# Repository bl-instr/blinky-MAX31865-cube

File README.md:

#    Blinky-MAX31864 Cube # 
The Blinky-MAX31865 cube is a precision 4 terminal resistance measurement device that integrates into a Blinky-Lite control platform. The cubes incorporates two [Adafruit MAX31865 breakout boards](https://www.adafruit.com/product/3648) providing two independent measurment channels with 15 bits of resolution

## Features: ##
- Seamless integration into the open source [Blinky-Lite control platform](https://www.blinky-lite.se/) 
- Wireless connection for data acquistion and control
- Web interface for wireless connection configuration
- Two independent channels
- Eighth order Chebyschev or power series temperature fit via web interface
- 100 mS pulsed measurements for low self heating
- User defined IIR filtering
- User defined measurement rate
- 15 bits of resolution

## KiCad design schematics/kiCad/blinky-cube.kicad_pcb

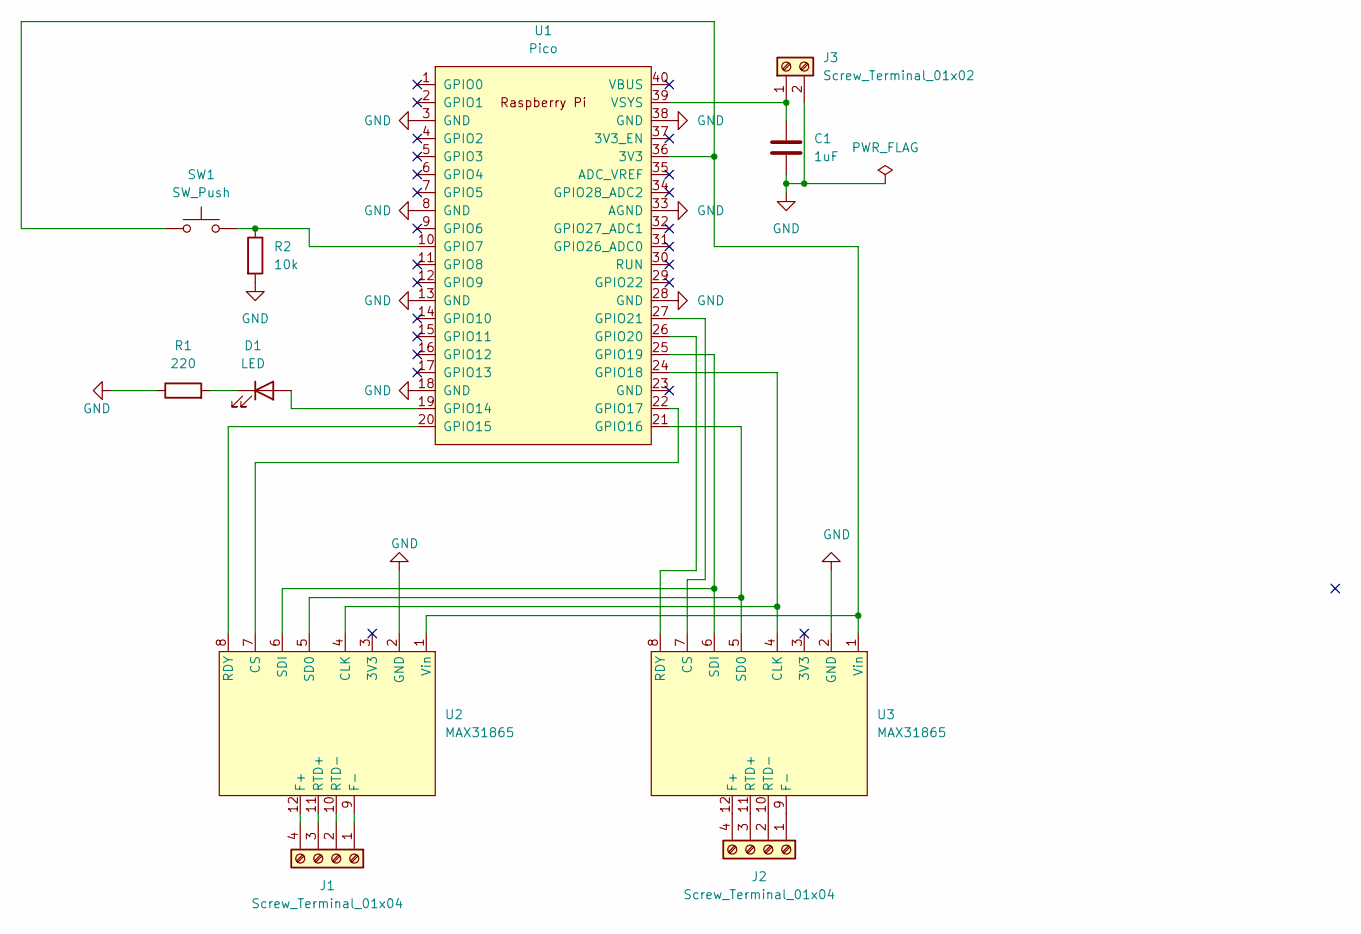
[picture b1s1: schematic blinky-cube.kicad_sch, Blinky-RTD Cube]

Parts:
C1: 1uF; C_Disc_D4.3mm_W1.9mm_P5.00mm
D1: LED; LED_D5.0mm
J1, J2: Screw_Terminal_01x04; TerminalBlock_bornier-4_P5.08mm
J3: Screw_Terminal_01x02; TerminalBlock_bornier-2_P5.08mm
R1: 220; R_Axial_DIN0207_L6.3mm_D2.5mm_P7.62mm_Horizontal
R2: 10k; R_Axial_DIN0207_L6.3mm_D2.5mm_P7.62mm_Horizontal
SW1: SW_Push; SW_PUSH_6mm
U1: Pico; RPi_Pico_SMD_TH
U2, U3: MAX31865

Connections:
GND: C1.2, J3.2, R1.1, R2.2, U1.3 (GND), U1.8 (GND), U1.13 (GND), U1.18 (GND), U1.28 (GND), U1.33 (AGND), U1.38 (GND), U2.2 (GND), U3.2 (GND)
unnamed: C1.1, J3.1, U1.39 (VSYS)
unnamed: D1.1 (K), R1.2
unnamed: J1.1, U2.9 (F-)
unnamed: J1.2, U2.10 (RTD-)
unnamed: J1.3, U2.11 (RTD+)
unnamed: J1.4, U2.12 (F+)
unnamed: J2.1, U3.9 (F-)
unnamed: J2.2, U3.10 (RTD-)
unnamed: J2.3, U3.11 (RTD+)
unnamed: J2.4, U3.12 (F+)
unnamed: R2.1, SW1.2, U1.10 (GPIO7)
unnamed: SW1.1, U1.36 (3V3), U2.1 (Vin), U3.1 (Vin)
unnamed: D1.2 (A), U1.19 (GPIO14)
unnamed: U1.21 (GPIO16), U2.5 (SD0), U3.5 (SD0)
unnamed: U1.22 (GPIO17), U2.7 (CS)
unnamed: U1.24 (GPIO18), U2.4 (CLK), U3.4 (CLK)
unnamed: U1.25 (GPIO19), U2.6 (SDI), U3.6 (SDI)
unnamed: U1.20 (GPIO15), U2.8 (RDY)
unnamed: U1.27 (GPIO21), U3.7 (CS)
unnamed: U1.26 (GPIO20), U3.8 (RDY)

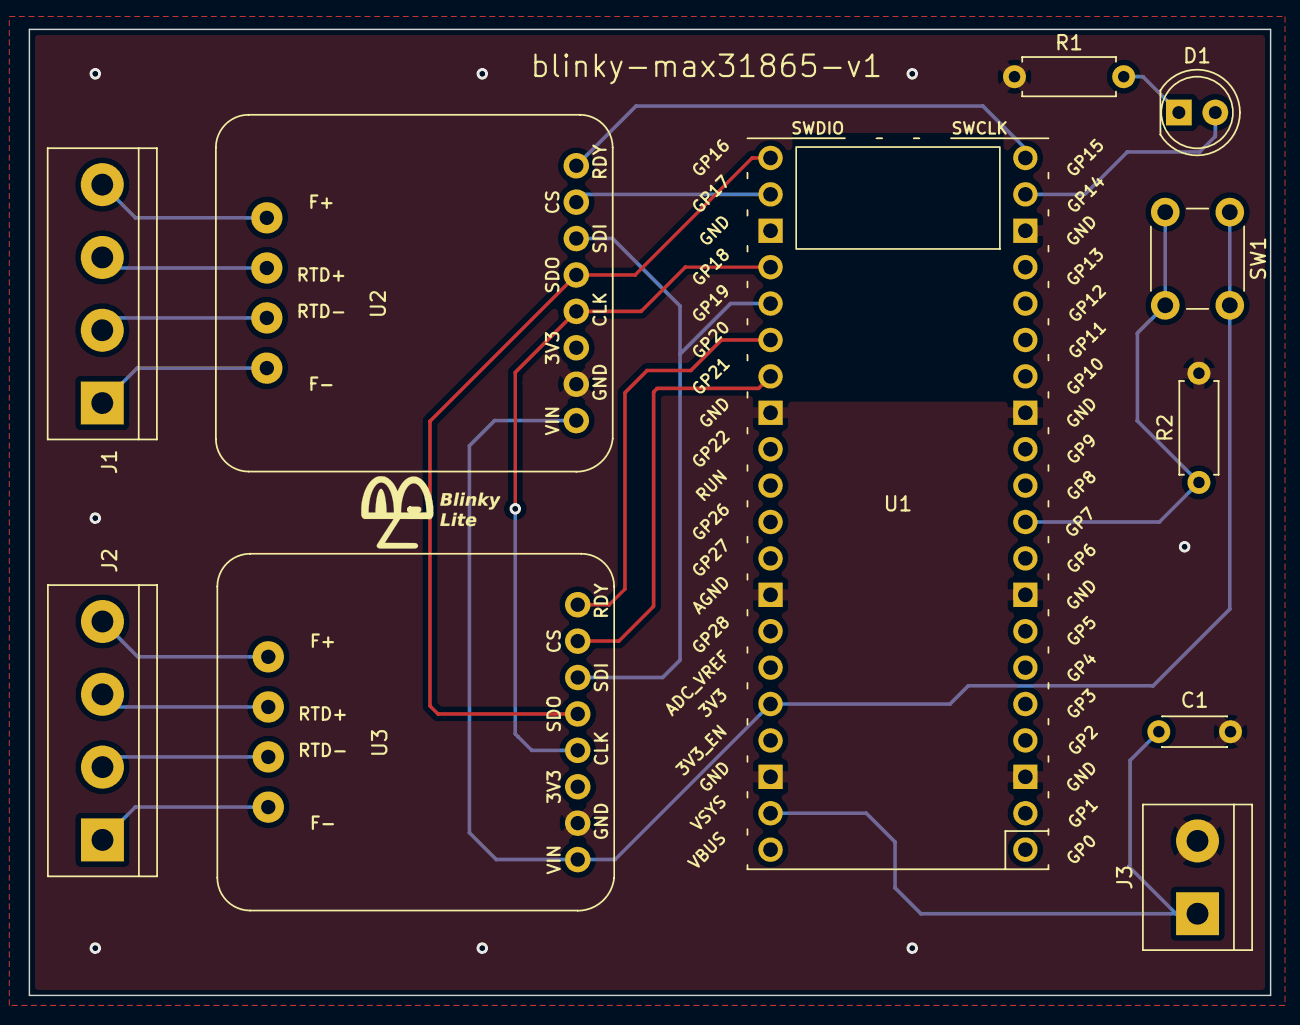
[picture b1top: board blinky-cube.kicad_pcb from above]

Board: 2 copper layers, 86.6 x 67.4 mm, 11 parts (0 on the bottom side), 21 nets.

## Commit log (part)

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2023-09-25 working python web page and talking to max31865
2023-09-29 mqtt hanging on ping
2023-09-29 working with tray
2023-10-05 working with 100 ms pulse
2023-10-26 added Readme
2024-03-03 added wifi reboot after too may attempts
2024-04-18 change to one-core
